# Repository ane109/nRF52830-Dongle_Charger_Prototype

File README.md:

# nRF52830-Dongle_Charger_Prototype
Li-Ion test circuitry for an nRF52830-Dongle board

## Details
- Supplies battery power to nRF52840-Dongle when USB power is unavailable.
- Physical disconnect switch for battery.
- I2C Coulumb counter to monitor charge state
- 1.8V Voltage regulator for future ICs

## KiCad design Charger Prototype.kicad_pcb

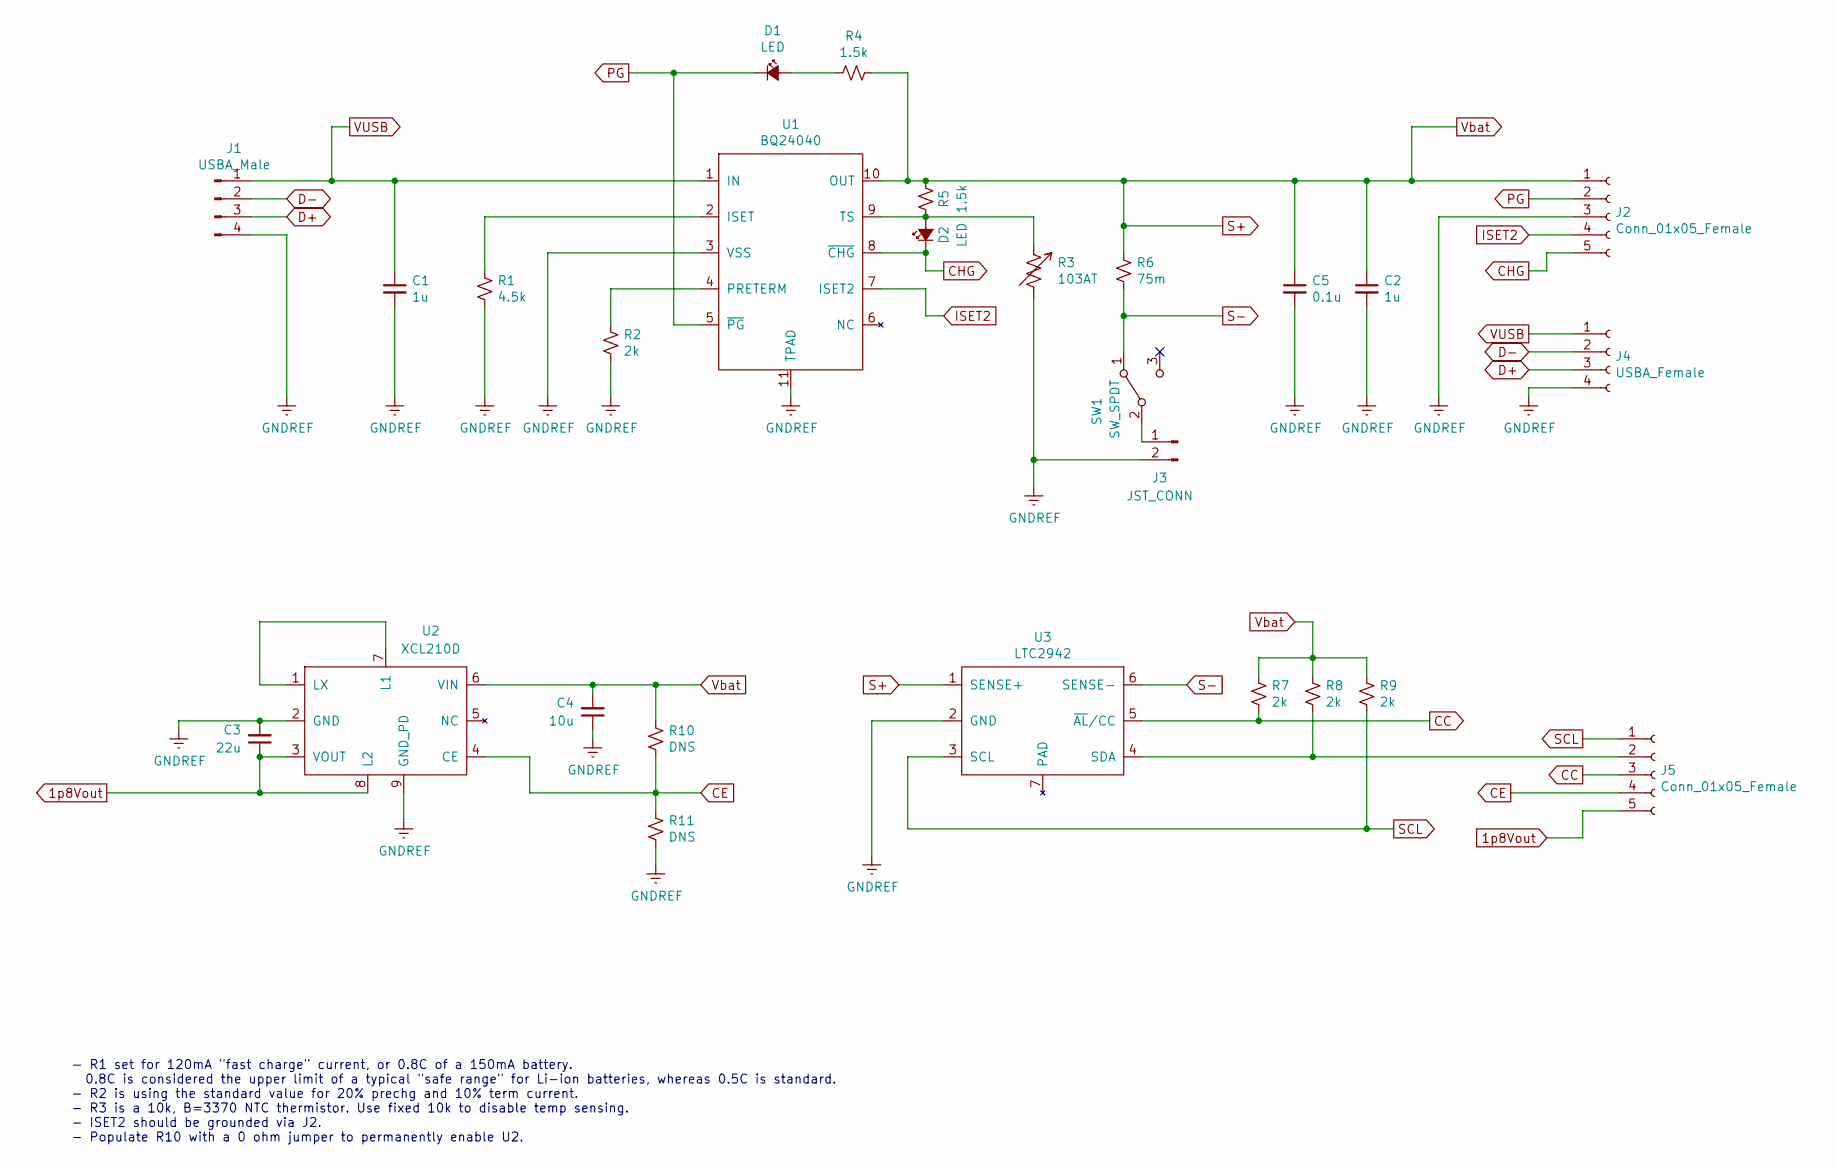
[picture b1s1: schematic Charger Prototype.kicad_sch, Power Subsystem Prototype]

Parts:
C1, C2: 1u; C_0603_1608Metric
C3: 22u; C_0603_1608Metric
C4: 10u; C_0603_1608Metric
C5: 0.1u; C_0603_1608Metric
D1, D2: LED; SML-D12
J1: USBA_Male; USB_Male_A_UP2-AH-1-TH_3d
J2, J5: Conn_01x05_Female; PinHeader_1x05_P1.27mm_Vertical
J3: JST_CONN; JST_PH_S2B-PH-K_1x02_P2.00mm_Horizontal
J4: USBA_Female; USB_A_Female_UE27AC54100_3d
R1: 4.5k; R_0603_1608Metric
R2, R7, R8, R9: 2k; R_0603_1608Metric
R3: 103AT; R_0805_2012Metric_Pad1.15x1.40mm_HandSolder
R4, R5: 1.5k; R_0603_1608Metric
R6: 75m; R_0805_2012Metric
R10, R11: DNS; R_0603_1608Metric
SW1: SW_SPDT; Wurth_SPDT_Slide_450301014042
U1: BQ24040; BQ24040_10mil
U2: XCL210D; XCL210_10mil
U3: LTC2942

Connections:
1p8Vout: C3.1, J5.5, U2.3 (VOUT), U2.8 (L2)
CC: J5.3, R7.2, U3.5 (~AL/CC)
CE: J5.4, R10.2, R11.1, U2.4 (CE)
CHG: D2.1 (K), J2.5, U1.8 (~CHG)
D+: J1.3, J4.3
D-: J1.2, J4.2
GNDREF: C1.2, C2.2, C3.2, C4.1, C5.2, J1.4, J2.3, J3.2, J4.4, R1.2, R2.2, R3.2, R11.2, U1.3 (VSS), U1.11 (TPAD), U2.2 (GND), U2.9 (GND_PD), U3.2 (GND)
ISET2: J2.4, U1.7 (ISET2)
unnamed: D1.2 (A), R4.2
unnamed: J3.1, SW1.2 (B)
unnamed: J5.2, R8.2, U3.4 (SDA)
unnamed: R1.1, U1.2 (ISET)
unnamed: R2.1, U1.4 (PRETERM)
unnamed: U2.1 (LX), U2.7 (L1)
PG: D1.1 (K), J2.2, U1.5 (~PG)
S+: C2.1, C4.2, C5.1, J2.1, R4.1, R5.2, R6.1, R7.1, R8.1, R9.1, R10.1, U1.10 (OUT), U2.6 (VIN), U3.1 (SENSE+)
S-: R6.2, SW1.1 (A), U3.6 (SENSE-)
SCL: J5.1, R9.2, U3.3 (SCL)
VUSB: C1.1, J1.1, J4.1, U1.1 (IN)

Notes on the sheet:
- R1 set for 120mA "fast charge" current, or 0.8C of a 150mA battery. 0.8C is considered the upper limit of a typical "safe range" for Li-ion batteries, whereas 0.5C is standard. - R2 is using the standard value for 20% prechg and 10% term current. - R3 is a 10k, B=3370 NTC thermistor. Use fixed 10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

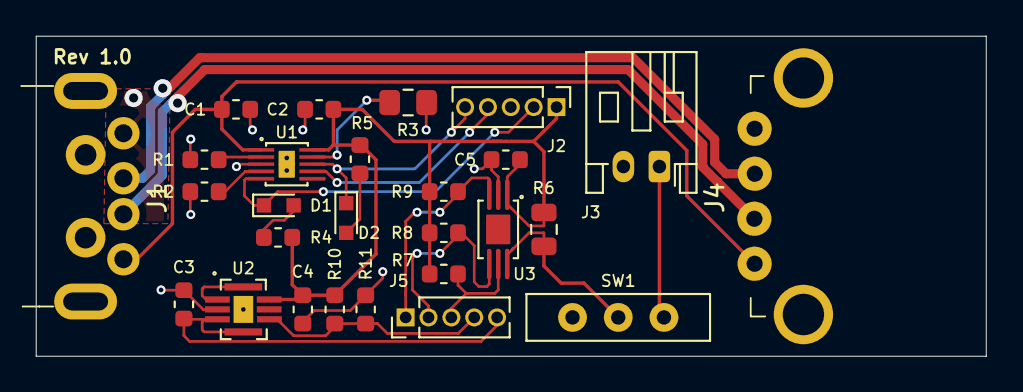
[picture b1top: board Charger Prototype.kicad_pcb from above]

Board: 2 copper layers, 52.8 x 17.8 mm, 27 parts (0 on the bottom side), 21 nets.

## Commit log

2025-05-28 Added files
    Design notes and images added. STLs for 3d-printable enclosure added.
2025-06-23 Rename Printing Print Schematic_full.png to Schematic_full.png
2025-06-23 Moved 3d_view.png to Media/3d_view.png
    Created Media folder
2025-06-23 Moved Charger_Dongle_Assy.jpg to Media/Charger_Dongle_Assy.jpg
2025-06-23 Moved Schematic_full.png to Media/Schematic_full.png
2025-06-23 Update README.md
    Added schematic and images
